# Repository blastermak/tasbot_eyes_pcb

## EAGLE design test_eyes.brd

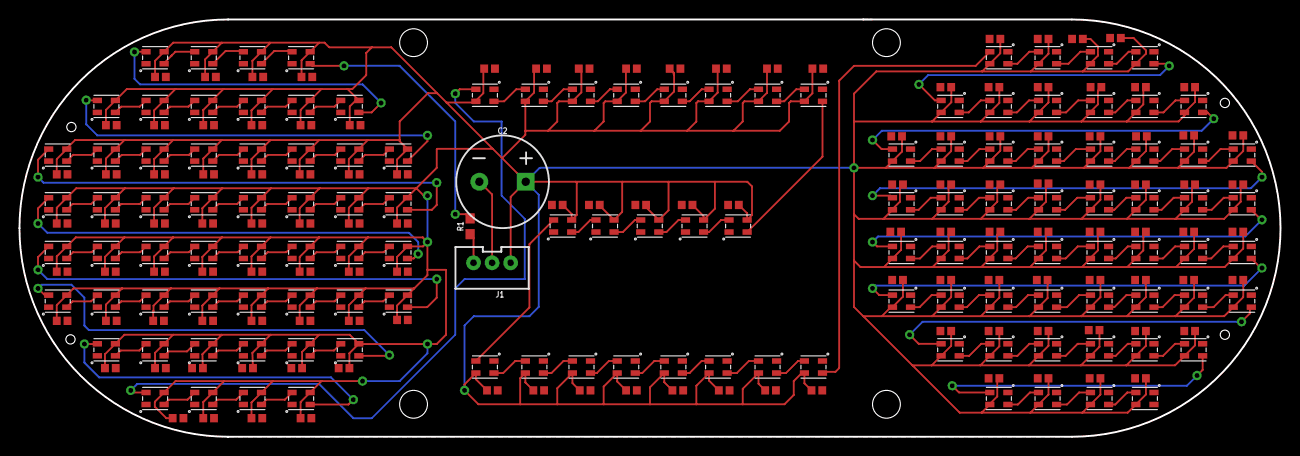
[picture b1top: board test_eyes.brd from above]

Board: 2 copper layers, 136.0 x 45.0 mm, 253 parts (0 on the bottom side), 128 nets.

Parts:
C1, C3, C4, C5, C6, C7, C8, C9, C10, C11, C12, C13, C14, C15, C16, C17, C18, C19, C20, C21, C22, C23, C24, C25, C26, C27, C28, C29, C30, C31, C32, C33, C34, C35, C36, C37, C38, C39, C40, C41, C42, C43, C44, C45, C46, C47, C48, C49, C50, C51, C52, C53, C54, C55, C56, C57, C58, C59, C60, C61, C62, C63, C64, C65, C66, C67, C68, C69, C70, C71, C72, C73, C74, C75, C76, C77, C78, C79, C80, C81, C82, C83, C84, C85, C86, C87, C88, C89, C90, C91, C92, C93, C94, C95, C96, C97, C98, C99, C100, C101, C102, C103, C104, C105, C106, C107, C108, C109, C110, C111, C112, C113, C114, C115, C116, C117, C118, C119, C120, C121, C122, C123, C124, C125, C126: 0.1uF; 0402
C2: 1mF; CPOL-RADIAL-5MM-10MM
J1: JST-3-PTH-VERT
R1: 470; 0603
U$1, U$2, U$3, U$4, U$5, U$6, U$7, U$8, U$9, U$10, U$11, U$12, U$13, U$14, U$15, U$16, U$17, U$18, U$19, U$20, U$21, U$22, U$23, U$24, U$25, U$26, U$27, U$28, U$29, U$30, U$31, U$32, U$33, U$34, U$35, U$36, U$37, U$38, U$39, U$40, U$41, U$42, U$43, U$44, U$45, U$46, U$47, U$48, U$49, U$50, U$51, U$52, U$53, U$54, U$55, U$56, U$57, U$58, U$59, U$60, U$61, U$62, U$63, U$64, U$65, U$66, U$67, U$68, U$69, U$70, U$71, U$72, U$73, U$74, U$75, U$76, U$77, U$78, U$79, U$80, U$81, U$82, U$83, U$84, U$85, U$86, U$87, U$88, U$89, U$90, U$91, U$92, U$93, U$94, U$95, U$96, U$97, U$98, U$99, U$100, U$101, U$102, U$103, U$104, U$105, U$106, U$107, U$108, U$109, U$110, U$111, U$112, U$113, U$114, U$115, U$116, U$117, U$118, U$119, U$120, U$121, U$122, U$123, U$124, U$125: NEOPIXEL_NANO_2427; SK6805-2427

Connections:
DIN: J1.3, R1.1
GND: C1.2, C2.-, C3.2, C4.1, C5.1, C6.1, C7.1, C8.2, C9.2, C10.2, C11.2, C12.2, C13.2, C14.2, C15.2, C16.2, C17.2, C18.2, C19.2, C20.2, C21.2, C22.2, C23.2, C24.2, C25.2, C26.2, C27.2, C28.2, C29.2, C30.2, C31.2, C32.2, C33.2, C34.2, C35.2, C36.2, C37.2, C38.2, C39.2, C40.2, C41.2, C42.2, C43.2, C44.2, C45.2, C46.2, C47.2, C48.2, C49.2, C50.2, C51.2, C52.2, C53.2, C54.2, C55.2, C56.2, C57.2, C58.2, C59.2, C60.2, C61.2, C62.2, C63.2, C64.2, C65.2, C66.2, C67.2, C68.2, C69.2, C70.2, C71.2, C72.2, C73.2, C74.2, C75.2, C76.2, C77.2, C78.2, C79.2, C80.2, C81.2, C82.2, C83.2, C84.2, C85.2, C86.2, C87.2, C88.2, C89.2, C90.2, C91.2, C92.2, C93.2, C94.2, C95.2, C96.2, C97.2, C98.2, C99.2, C100.2, C101.2, C102.2, C103.2, C104.2, C105.2, C106.2, C107.2, C108.2, C109.2, C110.2, C111.2, C112.2, C113.2, C114.2, C115.2, C116.2, C117.2, C118.2, C119.2, C120.2, C121.2, C122.2, C123.2, C124.2, C125.2, C126.2, J1.2, U$1.GND, U$2.GND, U$3.GND, U$4.GND, U$5.GND, U$6.GND, U$7.GND, U$8.GND, U$9.GND, U$10.GND, U$11.GND, U$12.GND, U$13.GND, U$14.GND, U$15.GND, U$16.GND, U$17.GND, U$18.GND, U$19.GND, U$20.GND, U$21.GND, U$22.GND, U$23.GND, U$24.GND, U$25.GND, U$26.GND, U$27.GND, U$28.GND, U$29.GND, U$30.GND, U$31.GND, U$32.GND, U$33.GND, U$34.GND, U$35.GND, U$36.GND, U$37.GND, U$38.GND, U$39.GND, U$40.GND, U$41.GND, U$42.GND, U$43.GND, U$44.GND, U$45.GND, U$46.GND, U$47.GND, U$48.GND, U$49.GND, U$50.GND, U$51.GND, U$52.GND, U$53.GND, U$54.GND, U$55.GND, U$56.GND, U$57.GND, U$58.GND, U$59.GND, U$60.GND, U$61.GND, U$62.GND, U$63.GND, U$64.GND, U$65.GND, U$66.GND, U$67.GND, U$68.GND, U$69.GND, U$70.GND, U$71.GND, U$72.GND, U$73.GND, U$74.GND, U$75.GND, U$76.GND, U$77.GND, U$78.GND, U$79.GND, U$80.GND, U$81.GND, U$82.GND, U$83.GND, U$84.GND, U$85.GND, U$86.GND, U$87.GND, U$88.GND, U$89.GND, U$90.GND, U$91.GND, U$92.GND, U$93.GND, U$94.GND, U$95.GND, U$96.GND, U$97.GND, U$98.GND, U$99.GND, U$100.GND, U$101.GND, U$102.GND, U$103.GND, U$104.GND, U$105.GND, U$106.GND, U$107.GND, U$108.GND, U$109.GND, U$110.GND, U$111.GND, U$112.GND, U$113.GND, U$114.GND, U$115.GND, U$116.GND, U$117.GND, U$118.GND, U$119.GND, U$120.GND, U$121.GND, U$122.GND, U$123.GND, U$124.GND, U$125.GND
unnamed: U$2.DOUT, U$3.DIN
unnamed: U$3.DOUT, U$4.DIN
unnamed: R1.2, U$1.DIN
unnamed: U$1.DOUT, U$2.DIN
unnamed: U$4.DOUT, U$5.DIN
unnamed: U$5.DOUT, U$6.DIN
unnamed: U$6.DOUT, U$7.DIN
unnamed: U$7.DOUT, U$8.DIN
unnamed: U$8.DOUT, U$9.DIN
unnamed: U$9.DOUT, U$10.DIN
unnamed: U$10.DOUT, U$11.DIN
unnamed: U$11.DOUT, U$12.DIN
unnamed: U$12.DOUT, U$13.DIN
unnamed: U$13.DOUT, U$14.DIN
unnamed: U$14.DOUT, U$15.DIN
unnamed: U$15.DOUT, U$16.DIN
unnamed: U$16.DOUT, U$17.DIN
unnamed: U$17.DOUT, U$18.DIN
unnamed: U$18.DOUT, U$19.DIN
unnamed: U$19.DOUT, U$20.DIN
unnamed: U$20.DOUT, U$21.DIN
unnamed: U$21.DOUT, U$22.DIN
unnamed: U$22.DOUT, U$23.DIN
unnamed: U$23.DOUT, U$24.DIN
unnamed: U$24.DOUT, U$25.DIN
unnamed: U$25.DOUT, U$26.DIN
unnamed: U$26.DOUT, U$27.DIN
unnamed: U$27.DOUT, U$28.DIN
unnamed: U$28.DOUT, U$29.DIN
unnamed: U$29.DOUT, U$30.DIN
unnamed: U$30.DOUT, U$31.DIN
unnamed: U$31.DOUT, U$32.DIN
unnamed: U$32.DOUT, U$33.DIN
unnamed: U$33.DOUT, U$34.DIN
unnamed: U$34.DOUT, U$35.DIN
unnamed: U$35.DOUT, U$36.DIN
unnamed: U$36.DOUT, U$37.DIN
unnamed: U$37.DOUT, U$38.DIN
unnamed: U$38.DOUT, U$39.DIN
unnamed: U$39.DOUT, U$40.DIN
unnamed: U$40.DOUT, U$41.DIN
unnamed: U$41.DOUT, U$42.DIN
unnamed: U$42.DOUT, U$43.DIN
unnamed: U$43.DOUT, U$44.DIN
unnamed: U$44.DOUT, U$45.DIN
unnamed: U$45.DOUT, U$46.DIN
unnamed: U$46.DOUT, U$47.DIN
unnamed: U$47.DOUT, U$48.DIN
unnamed: U$48.DOUT, U$49.DIN
unnamed: U$49.DOUT, U$50.DIN
unnamed: U$50.DOUT, U$51.DIN
unnamed: U$51.DOUT, U$52.DIN
unnamed: U$52.DOUT, U$66.DIN
unnamed: U$60.DOUT, U$74.DIN
unnamed: U$74.DOUT, U$75.DIN
unnamed: U$75.DOUT, U$76.DIN
unnamed: U$76.DOUT, U$77.DIN
unnamed: U$77.DOUT, U$78.DIN
unnamed: U$78.DOUT, U$79.DIN
unnamed: U$79.DOUT, U$80.DIN
unnamed: U$80.DOUT, U$81.DIN
unnamed: U$81.DOUT, U$82.DIN
unnamed: U$82.DOUT, U$83.DIN
unnamed: U$83.DOUT, U$84.DIN
unnamed: U$66.DOUT, U$67.DIN
unnamed: U$67.DOUT, U$68.DIN
unnamed: U$68.DOUT, U$69.DIN
unnamed: U$69.DOUT, U$70.DIN
unnamed: U$70.DOUT, U$71.DIN
unnamed: U$71.DOUT, U$72.DIN
unnamed: U$72.DOUT, U$73.DIN
unnamed: U$84.DOUT, U$85.DIN
unnamed: U$85.DOUT, U$86.DIN
unnamed: U$86.DOUT, U$87.DIN
unnamed: U$87.DOUT, U$88.DIN
unnamed: U$88.DOUT, U$89.DIN
unnamed: U$89.DOUT, U$90.DIN
unnamed: U$91.DOUT, U$92.DIN
unnamed: U$92.DOUT, U$93.DIN
unnamed: U$93.DOUT, U$94.DIN
unnamed: U$94.DOUT, U$95.DIN
unnamed: U$95.DOUT, U$96.DIN
unnamed: U$61.DIN, U$73.DOUT
unnamed: U$61.DOUT, U$62.DIN
unnamed: U$96.DOUT, U$97.DIN
unnamed: U$62.DOUT, U$63.DIN
unnamed: U$63.DOUT, U$64.DIN
unnamed: U$64.DOUT, U$65.DIN
unnamed: U$53.DIN, U$65.DOUT
unnamed: U$53.DOUT, U$54.DIN
unnamed: U$54.DOUT, U$55.DIN
unnamed: U$55.DOUT, U$56.DIN
unnamed: U$56.DOUT, U$57.DIN
unnamed: U$57.DOUT, U$58.DIN
unnamed: U$58.DOUT, U$59.DIN
unnamed: U$59.DOUT, U$60.DIN
unnamed: U$97.DOUT, U$98.DIN
unnamed: U$98.DOUT, U$99.DIN
unnamed: U$99.DOUT, U$100.DIN
unnamed: U$100.DOUT, U$101.DIN
unnamed: U$101.DOUT, U$102.DIN
unnamed: U$102.DOUT, U$103.DIN
unnamed: U$103.DOUT, U$104.DIN
unnamed: U$104.DOUT, U$105.DIN
unnamed: U$105.DOUT, U$106.DIN
unnamed: U$106.DOUT, U$107.DIN
unnamed: U$107.DOUT, U$108.DIN
unnamed: U$108.DOUT, U$109.DIN
unnamed: U$109.DOUT, U$110.DIN
unnamed: U$110.DOUT, U$111.DIN
unnamed: U$111.DOUT, U$112.DIN
unnamed: U$112.DOUT, U$113.DIN
unnamed: U$113.DOUT, U$114.DIN
unnamed: U$114.DOUT, U$115.DIN
unnamed: U$115.DOUT, U$116.DIN
unnamed: U$116.DOUT, U$117.DIN
unnamed: U$117.DOUT, U$118.DIN
unnamed: U$118.DOUT, U$119.DIN
unnamed: U$119.DOUT, U$120.DIN
unnamed: U$120.DOUT, U$121.DIN
unnamed: U$121.DOUT, U$122.DIN
unnamed: U$122.DOUT, U$123.DIN
unnamed: U$123.DOUT, U$124.DIN
unnamed: U$124.DOUT, U$125.DIN
unnamed: U$90.DOUT, U$91.DIN
VCC: C1.1, C2.+, C3.1, C4.2, C5.2, C6.2, C7.2, C8.1, C9.1, C10.1, C11.1, C12.1, C13.1, C14.1, C15.1, C16.1, C17.1, C18.1, C19.1, C20.1, C21.1, C22.1, C23.1, C24.1, C25.1, C26.1, C27.1, C28.1, C29.1, C30.1, C31.1, C32.1, C33.1, C34.1, C35.1, C36.1, C37.1, C38.1, C39.1, C40.1, C41.1, C42.1, C43.1, C44.1, C45.1, C46.1, C47.1, C48.1, C49.1, C50.1, C51.1, C52.1, C53.1, C54.1, C55.1, C56.1, C57.1, C58.1, C59.1, C60.1, C61.1, C62.1, C63.1, C64.1, C65.1, C66.1, C67.1, C68.1, C69.1, C70.1, C71.1, C72.1, C73.1, C74.1, C75.1, C76.1, C77.1, C78.1, C79.1, C80.1, C81.1, C82.1, C83.1, C84.1, C85.1, C86.1, C87.1, C88.1, C89.1, C90.1, C91.1, C92.1, C93.1, C94.1, C95.1, C96.1, C97.1, C98.1, C99.1, C100.1, C101.1, C102.1, C103.1, C104.1, C105.1, C106.1, C107.1, C108.1, C109.1, C110.1, C111.1, C112.1, C113.1, C114.1, C115.1, C116.1, C117.1, C118.1, C119.1, C120.1, C121.1, C122.1, C123.1, C124.1, C125.1, C126.1, J1.1, U$1.VCC, U$2.VCC, U$3.VCC, U$4.VCC, U$5.VCC, U$6.VCC, U$7.VCC, U$8.VCC, U$9.VCC, U$10.VCC, U$11.VCC, U$12.VCC, U$13.VCC, U$14.VCC, U$15.VCC, U$16.VCC, U$17.VCC, U$18.VCC, U$19.VCC, U$20.VCC, U$21.VCC, U$22.VCC, U$23.VCC, U$24.VCC, U$25.VCC, U$26.VCC, U$27.VCC, U$28.VCC, U$29.VCC, U$30.VCC, U$31.VCC, U$32.VCC, U$33.VCC, U$34.VCC, U$35.VCC, U$36.VCC, U$37.VCC, U$38.VCC, U$39.VCC, U$40.VCC, U$41.VCC, U$42.VCC, U$43.VCC, U$44.VCC, U$45.VCC, U$46.VCC, U$47.VCC, U$48.VCC, U$49.VCC, U$50.VCC, U$51.VCC, U$52.VCC, U$53.VCC, U$54.VCC, U$55.VCC, U$56.VCC, U$57.VCC, U$58.VCC, U$59.VCC, U$60.VCC, U$61.VCC, U$62.VCC, U$63.VCC, U$64.VCC, U$65.VCC, U$66.VCC, U$67.VCC, U$68.VCC, U$69.VCC, U$70.VCC, U$71.VCC, U$72.VCC, U$73.VCC, U$74.VCC, U$75.VCC, U$76.VCC, U$77.VCC, U$78.VCC, U$79.VCC, U$80.VCC, U$81.VCC, U$82.VCC, U$83.VCC, U$84.VCC, U$85.VCC, U$86.VCC, U$87.VCC, U$88.VCC, U$89.VCC, U$90.VCC, U$91.VCC, U$92.VCC, U$93.VCC, U$94.VCC, U$95.VCC, U$96.VCC, U$97.VCC, U$98.VCC, U$99.VCC, U$100.VCC, U$101.VCC, U$102.VCC, U$103.VCC, U$104.VCC, U$105.VCC, U$106.VCC, U$107.VCC, U$108.VCC, U$109.VCC, U$110.VCC, U$111.VCC, U$112.VCC, U$113.VCC, U$114.VCC, U$115.VCC, U$116.VCC, U$117.VCC, U$118.VCC, U$119.VCC, U$120.VCC, U$121.VCC, U$122.VCC, U$123.VCC, U$124.VCC, U$125.VCC

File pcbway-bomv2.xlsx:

No. | part number/description | Package | Value | Qty | RefDefs | Note
1 | CAP-0402 | 0402 | 0.1uF | 125 | C1, C3-126
2 | 470 ohm resistor | 0603 | 470 ohm | 1 | R1
3 | Neopixel 2427 package | SK6805-2427 | NEOPIXEL_NANO_2427 | 125 | U$1 - U$125
 | PCBWay PCB Assembly Service

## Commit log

2020-03-17 Added gitignore
2020-03-17 Removed unwanted files from repo
2020-03-17 Removed half of decoupling caps for cost reduction
2020-03-24 Added locations for mounting holes
2020-03-25 Latest version

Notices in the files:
parts and their libraries:
SparkFun-Connectors: Licensing: Creative Commons ShareAlike 4.0 International - https://creativecommons.org/licenses/by-sa/4.0
